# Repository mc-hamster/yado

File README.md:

# yado (Pronounced Yah-Dew)
"Yet Another Door Opener" ... ESP8266 based Door Controller with JSON REST API and Secure Password ACL. Intened for Garage Doors and Electronic Gate "Buzzers".

## Features

1. Open hardware available in ./hardware
 1. PCB available for purchase at OSHPark
  1. https://www.oshpark.com/shared_projects/0cBHd21f
 2. Full BOM available with distributor list.
  1. (See BOM in ./hardware for part list)
 3. Utilizes nodemcu dev board (It includes many components and just $7 on ebay)
 4. Supports both v0.9 and v1.0 nodemcu footprints. 
   1. http://www.aliexpress.com/wholesale?shipCountry=us&shipFromCountry=&shipCompanies=&SearchText=nodemcu&exception=&minPrice=&maxPrice=&minQuantity=&maxQuantity=&isFreeShip=n&isFavorite=n&isRtl=yes&isOnSale=n&isBigSale=n&similar_style=n&similar_style_id=&isAtmOnline=n&CatId=0&g=y&SortType=total_tranpro_desc&initiative_id=SB_20150717073819&isPremium=y&filterCat=400103%2C515%2C4099&needQuery=n&groupsort=1
1. Open source code available in ./src.
2. Completed Features:
 1. Digest based authentication (No clear text passwords) ... Done
 2. Support for DHCP & Static addresses ... Done
 3. JSON REST API to read door sensors ... Done
 4. Serve all javascript libaries locally ... Done
3. In progress
 1. JSON REST API
  1. Open/Close door ... In progress
  2. Contact Sensor status ... Done
  3. New server digest and payload ... Done
 2. Web Admin Interface for configuration ... In progress
  1. Captive portal ... Done
   1.. Note: DNS server library is unreliable. May cause ESP8266 watchdog reset.

## JSON REST

1. /json/sensors
 1. Return state of the sensors
2. /json/digest/new
 1. Generate a new server digest and associated time

## To build code

1. Install Arduino IDE (It's a horrible environment, but easiest to get going): http://arduino.cc
2. Install board support for the ESP8266: https://github.com/esp8266/Arduino
 1. Select your NodeMCU from the board menu.
3. Install  USB to TTL Bridge Drivers
 1. CH341 : http://www.electrodragon.com/w/CH341 (older nodemcu)
 2. CP2102 : Mac - Drivers built in. Windows - Use windows update. (newer nodemcu)
4. Load the Yagdo code into the Arduino IDE
5. Compile and load the code into your nodemcu dev board.

### Optional

1. Install Atmel Studio and Visual Micro. This is a better IDE than the Arduino IDE.

## Usage: Admin interface

1. Provide power to Yado
2. The LED1 will light solid for a few seconds. During this period, hold down the "user_flash" button.
3. Onces you press the button, LED1 will turn off.
4. When LED2 blinks. Let go of "user_flash".
5. Connect to the Yado access point.
 1. SSID: yado_admin
 2. Password: yado_admin
6. Point your browser to http://192.168.4.1
7. If this is your first time, select the "Load Defaults" link from main menu.

LED2 will continue to blink while Yado is in admin mode. Because unsecured networks are a bad idea, we have conciously decided not to support unsecured Access Points and they won't be listed in the WiFi configuration. Adding support will be a 3 line change, but let's not do it.

Using static IP addresses is recommended, but DHCP also works. The assigned DHCP address is available through the USB serial console (115200, 8n1) on startup, through your home router's interface or you can scan the network for Yado.

Important Note: You will have 30 minutes to make your changes. After 30 minutes, Yado will return to the default operation.

## Usage: Normal Interface

1. Point your web browser to Yado's IP address.
2. Type your access password and click 'open'.

## Usage: Installation

1. Connect the terminal labled "Open1" to your garage door opener.
2. Install an optional door sensor to "Sens1" or "Sens2".

Open2 is not used. Adding support it will some (very) minimal effort, but the UI will need to be kept simple.

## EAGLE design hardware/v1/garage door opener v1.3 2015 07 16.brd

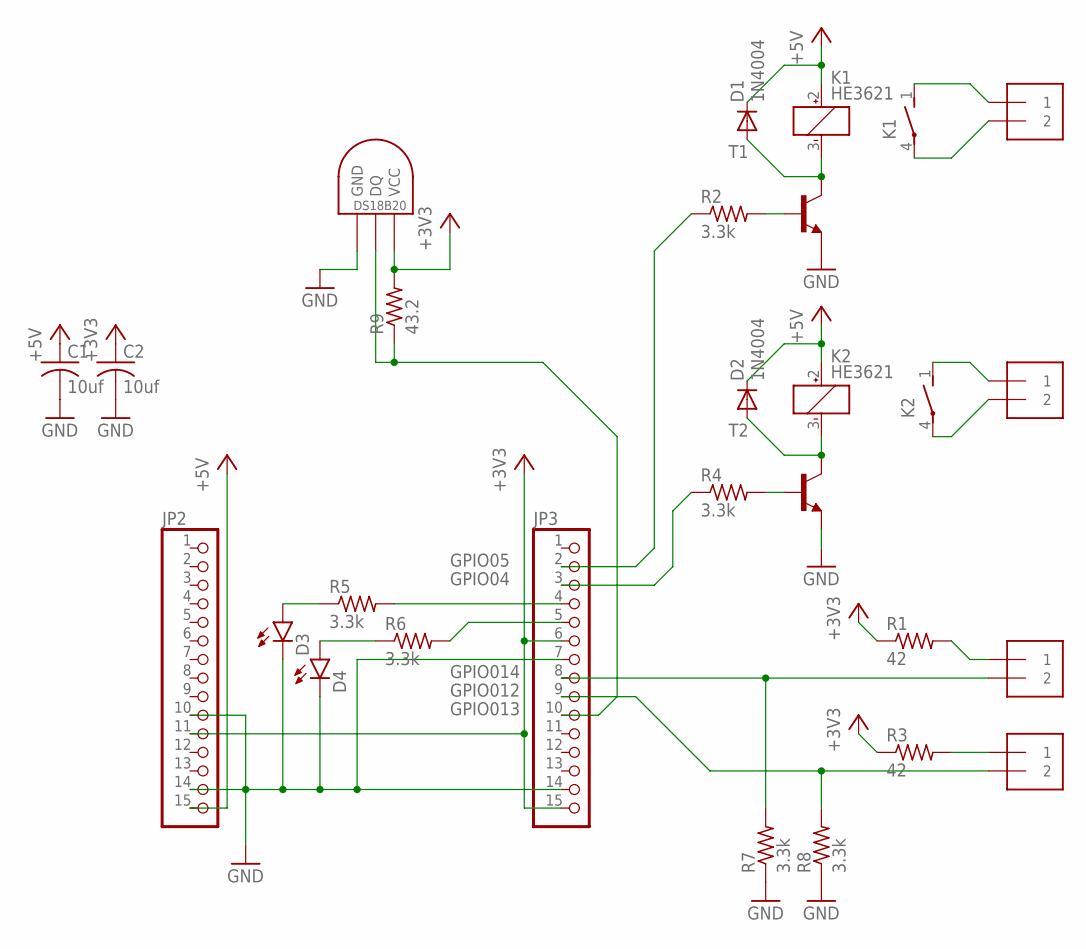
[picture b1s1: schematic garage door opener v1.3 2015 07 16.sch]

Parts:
C1, C2: 10uf; C0603
D1, D2: 1N4004; DO214BA
D3, D4: LED0603; LED-0603
DS18B20: DS18B20TO92; DS1820
JP2, JP3: PINHD-1X15; 1X15
K1, K2: HE3621; MPN HE3621A0510
OPEN1, OPEN2: 1X2-3.5MM; MPN OSTTE020161
R1, R3: 42; R0603
R2, R4, R5, R6, R7, R8: 3.3k; R0603
R9: 43.2; R0603
SENS1, SENS2: 1X2-3.5MM; MPN OSTTE020161
T1, T2: MMBT3904LT1-NPN-SOT23-BEC; SOT23-BEC; MPN MMBT2222A

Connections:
+3V3: C2.1, DS18B20.VDD (VCC), JP2.11, JP3.6, JP3.15, R1.1, R3.1, R9.2
+5V: C1.1, D1.C, D2.C, JP2.15, K1.2 (+), K2.2 (+)
GND: C1.2, C2.2, D3.C, D4.C, DS18B20.GND, JP2.10, JP2.14, JP3.7, JP3.14, R7.1, R8.1, T1.E, T2.E
unnamed: K1.1 (S), OPEN1.1
unnamed: K1.4, OPEN1.2
unnamed: JP3.8, R7.2, SENS1.2
unnamed: R1.2, SENS1.1
unnamed: D1.A, K1.3 (-), T1.C
unnamed: JP3.2, R2.1
unnamed: R2.2, T1.B
unnamed: JP3.4, R5.2
unnamed: JP3.5, R6.2
unnamed: R3.2, SENS2.1
unnamed: JP3.9, R8.2, SENS2.2
unnamed: K2.1 (S), OPEN2.1
unnamed: K2.4, OPEN2.2
unnamed: D2.A, K2.3 (-), T2.C
unnamed: JP3.3, R4.1
unnamed: R4.2, T2.B
unnamed: D4.A, R6.1
unnamed: D3.A, R5.1
unnamed: DS18B20.DQ, JP3.10, R9.1

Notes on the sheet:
GPIO05
GPIO04
GPIO014
GPIO012
GPIO013

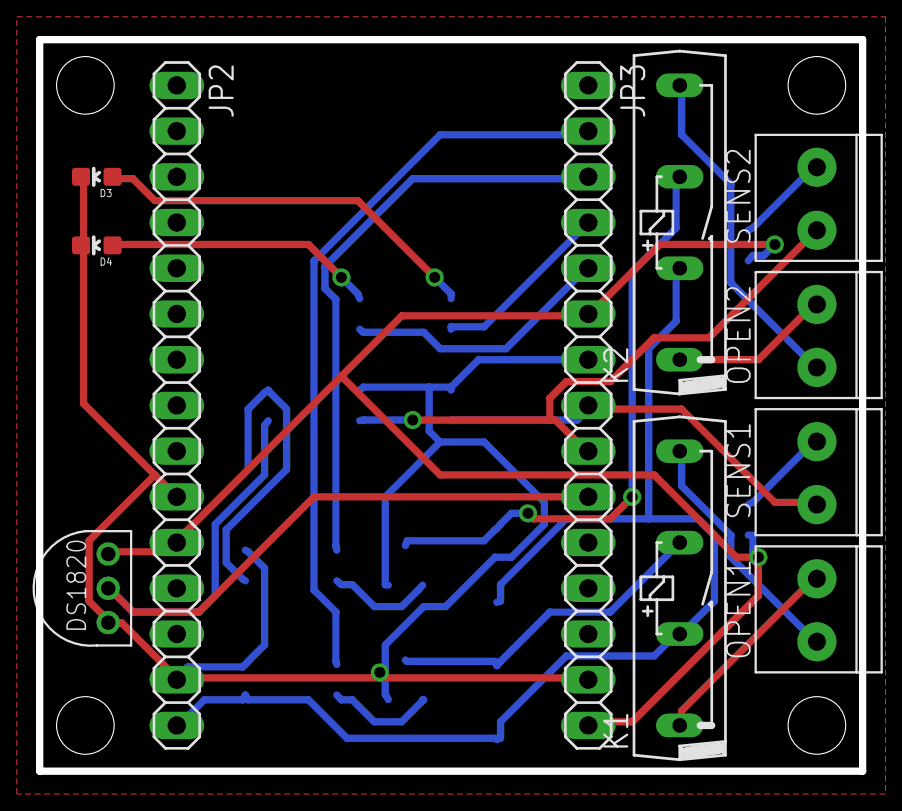
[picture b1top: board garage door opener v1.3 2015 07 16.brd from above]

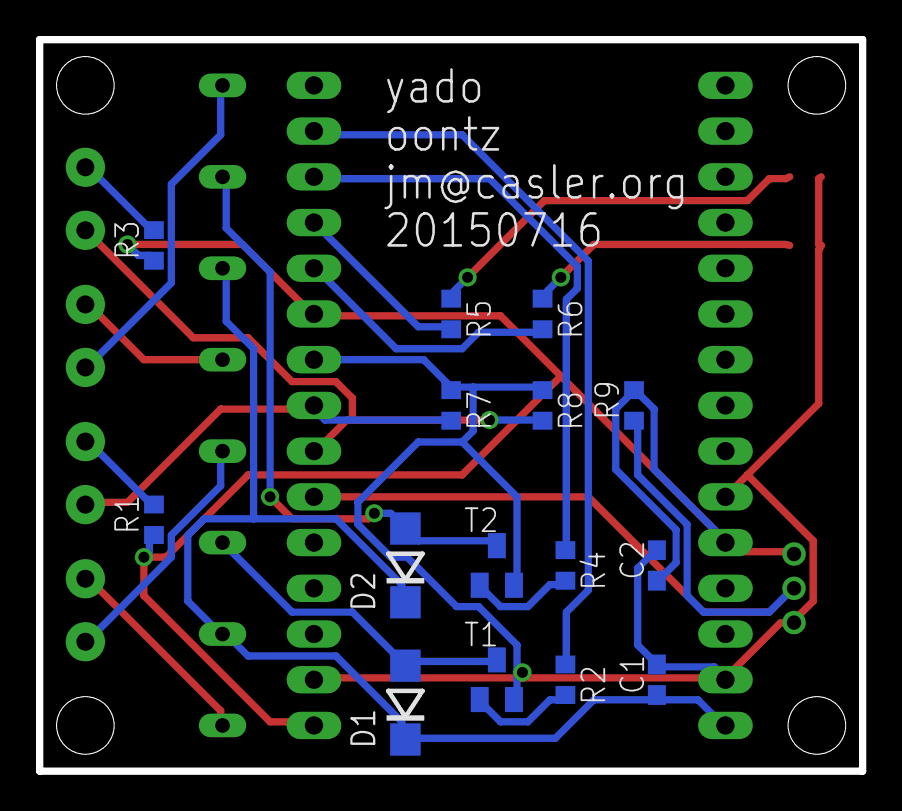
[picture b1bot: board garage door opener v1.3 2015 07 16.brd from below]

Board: 2 copper layers, 45.7 x 40.6 mm, 26 parts (15 on the bottom side), 22 nets.

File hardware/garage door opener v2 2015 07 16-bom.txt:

Partlist exported from /Users/jmcasler/Documents/CloudStation/projects/yado/hardware/garage door opener v2 2015 07 16.sch at 7/17/15 12:47 AM

Part    Value       Device                    Package   Description                MF     MPN         OC_FARNELL OC_NEWARK
C1      10uf        C-USC0603                 C0603     CAPACITOR, American symbol                                        
C2      10uf        C-USC0603                 C0603     CAPACITOR, American symbol                                        
D1      1N4004      DIODE-DO214BA             DO214BA   DIODE                                                             
D2      1N4004      DIODE-DO214BA             DO214BA   DIODE                                                             
D3                  LED0603                   LED-0603  LEDs                                                              
D4                  LED0603                   LED-0603  LEDs                                                              
DS18B20 DS18B20TO92 DS1820TO92                DS1820    DS18B20                                                           
JP1                 PINHD-1X15                1X15      PIN HEADER                                                        
JP2                 PINHD-1X15                1X15      PIN HEADER                                                        
JP3                 PINHD-1X15                1X15      PIN HEADER                                                        
K1      HE3621      HE3621                    HE3621    RELAY                      HAMLIN HE3621A0510 9561943    50F7993  
K2      HE3621      HE3621                    HE3621    RELAY                      HAMLIN HE3621A0510 9561943    50F7993  
OPEN1   1X2-3.5MM   1X2-3.5MM                 1X2-3.5MM 3.5mm Terminal block              OSTTE020161                     
OPEN2   1X2-3.5MM   1X2-3.5MM                 1X2-3.5MM 3.5mm Terminal block              OSTTE020161                     
R1      42          R-US_R0603                R0603     RESISTOR, American symbol                                         
R2      3.3k        R-US_R0603                R0603     RESISTOR, American symbol                                         
R3      42          R-US_R0603                R0603     RESISTOR, American symbol                                         
R4      3.3k        R-US_R0603                R0603     RESISTOR, American symbol                                         
R5      3.3k        R-US_R0603                R0603     RESISTOR, American symbol                                         
R6      3.3k        R-US_R0603                R0603     RESISTOR, American symbol                                         
R7      3.3k        R-US_R0603                R0603     RESISTOR, American symbol                                         
R8      3.3k        R-US_R0603                R0603     RESISTOR, American symbol                                         
R9      3.3k        R-US_R0603                R0603     RESISTOR, American symbol                                         
SENS1   1X2-3.5MM   1X2-3.5MM                 1X2-3.5MM 3.5mm Terminal block              OSTTE020161                     
SENS2   1X2-3.5MM   1X2-3.5MM                 1X2-3.5MM 3.5mm Terminal block              OSTTE020161                     
T1                  MMBT3904LT1-NPN-SOT23-BEC SOT23-BEC NPN Transistror                   MMBT2222A                       
T2                  MMBT3904LT1-NPN-SOT23-BEC SOT23-BEC NPN Transistror                   MMBT2222A

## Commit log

2015-06-18 Initial check in of Eagle files.
2015-06-18 Updated with BOM
2015-06-19 Updated with pull down resistor for sense inputs.
2015-06-19 Initial checkin of YAGDO -- Yet Another Garage Door Opener
2015-06-20 Update README.md
    Added build instructions
2015-06-20 Update README.md
    Added .md formatting
2015-06-23 Lots of refactoring
2015-06-25 renaming main file
2015-06-25 moved to a new directory
2015-06-27 Added ability to reboot from serial console.
2015-06-27 More generalized defaults
2015-06-27 Removed trough hole diode, removed top silkscreen, rerouted.
2015-06-27 removed through hole diode
2015-06-27 Removed power pads from left (not really needed?). Replaced LEDs with a proper LED footprint. Moved capacitors closer to headers.
2015-06-27 removed power header. swapped footprint for led.
2015-06-28 Set sensor inputs to INPUT rather than INPUT_PULLDOWN. Print MAC address to USB on boot.
2015-07-01 Switched from triggering watchdog to calling the ESP.reset() method.
2015-07-01 refactoring of web application to optimize sha1 computation
2015-07-01 No longer using INPUT_PULLDOWN. While it's in the SDK, it's not implemented by the silicon.
2015-07-03 Refactored password verification into webUtilities.
2015-07-04 Changed the mime type of json responses. Added error feedback to web browser.
2015-07-04 Refactored reading the sensors to return human readable strings.
2015-07-04 fixed rest response. forgot to quote the string. also added ability to invert the response from the door sensors. this is to support both NC and NO type contacts.
2015-07-06 Updated with footprint for ds18b20 ... why? feature creep!
2015-07-13 Moved most settings into the settings_t structure. This will allow us to easily save it to eeprom. Also begin support for multiple accounts.
2015-07-13 Updated defaults file.
2015-07-13 Fixed static / dynamic ip selection
2015-07-13 Adding href around the site title. Useful for debugging.
2015-07-13 Only process password if requestPassword is not an empty string.
2015-07-13 Support for multiple passwords.
2015-07-13 esp8266WebServer has a limit on file size for response content of ~2.5k. Started using the client method of the server to handle the response directly. Now can serve ~25k without much issue.
2015-07-17 Support for an admin mode to make config changes - After power on, LED1 will light for 5 seconds. During this period, hold down the user_flash button. LED2 will start to blink. Release the button onc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
2015-07-17 If we've been in admin mode for 30 minutes, reboot to get out of admin mode.
2015-07-17 Updated read
2015-07-17 Updated PCB. Removed power test points on left. Moved most surface mount components onto the back of the board. Switched to using just two resistor values (easier to source components).
2015-07-17 BOM and PDF of schematic / board.
2015-07-17 this didn't need to be checked in.
2015-07-17 no message
2015-07-17 Updated indenting to make it easier to read.
2015-07-17 Updated with admin pages that scans for wifi ap and prints settings.
2015-07-18 Lots of changes to admin mode.
2015-07-18 More admin UI
2015-07-19 Admin interface for configuration works! Yippie!
2015-07-19 rename defaults method to loadDefaults
2015-07-19 Added default values for the access note, writing settings now displays statistics about eeprom usage, increased size of access note.
2015-07-19 Added data structure to store configuration on contact sensors.
2015-07-19 Reformatted code.
2015-07-19 Deleting files, these will be moved to a new location
2015-07-19 Moved to v1 folder.
2015-08-06 fixed a typo
2015-08-06 removed unused menu items. it's been neutered.
2015-08-06 Enabled a captive portal for the admin mode.
2015-08-06 Added frameset for admin mode. Add display of basic flash statistics.
2015-08-06 Added support for frameset.
2015-08-21 defaults - Automatically load defaults on initial start up. Change default IP address & gateway. serialMenu - Deprecated serialMenu. This should not be needed. It's easier to use the web interface. w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
2015-08-21 Updated documentation in the realm
2015-08-21 Fixed missing semicolon
2015-08-22 Cleaned left nav.
2015-08-22 Hide the number of bytes written to eeprom. It can still be viewed by doing a view-source on the apply page.
2016-05-07 Updated to support the new ESP8266 v2.0.0 Arduino Library.
2016-05-07 Changed value of DS18B20 pull up resistor. Change is insignificant and the old part will continue to work.
2016-05-11 Google has stopped hosting the CryptoJS library. The original developer (Jeff Mott) no longer supports it on Google Code. Yado updated to a locally served version.
2016-05-15 renamed server object to httpServer. Implemented bonjour service discovery. Implemented http://yado.local/update when in admin mode for firmware updates.
2016-05-15 add link to /update from within admin
2016-05-15 removed sendMime function and replaced it with the httpserver.send function. esp8266webserver library now performs as expected.

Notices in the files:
parts and their libraries:
SparkFun-LED: Licensing: Creative Commons ShareAlike 4.0 International - https://creativecommons.org/licenses/by-sa/4.0
